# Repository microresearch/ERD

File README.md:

# ERD

ERD/ERD and ERD/SIR eurorack modules design and code files...

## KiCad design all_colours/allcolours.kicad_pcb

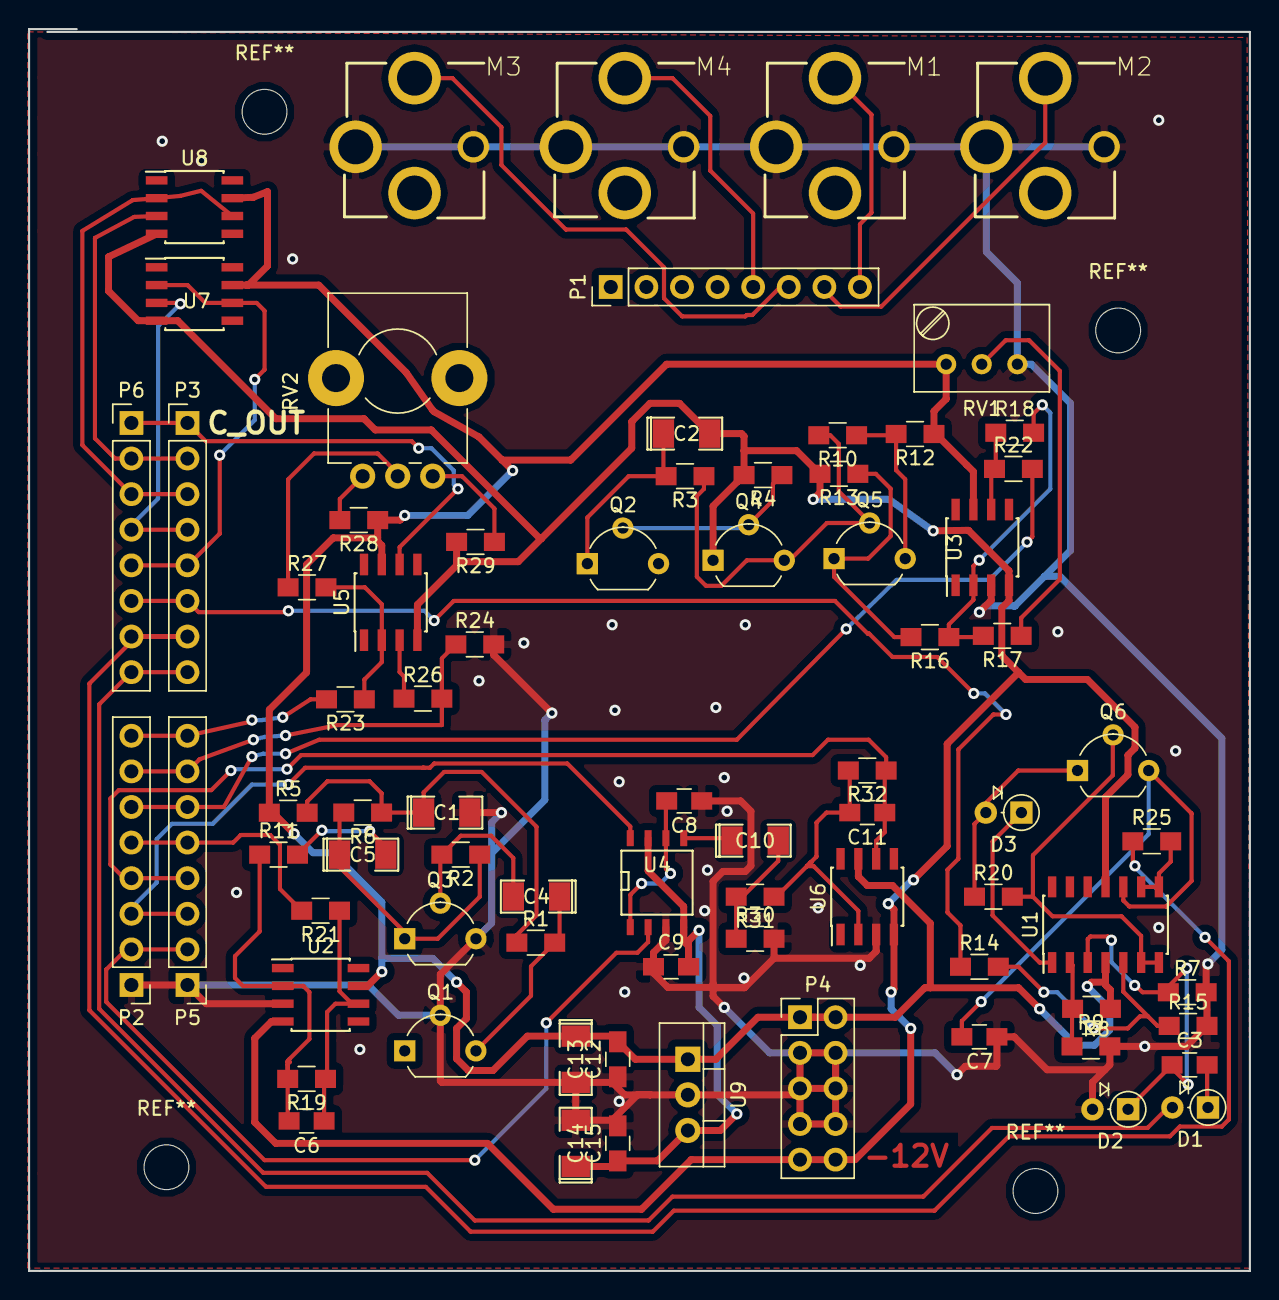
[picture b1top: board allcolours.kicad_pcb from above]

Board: 2 copper layers, 87.1 x 88.6 mm, 77 parts (0 on the bottom side), 56 nets.

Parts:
C1, C4: 47u; SMD-1206_Pol
C2, C5, C10, C13, C14: 10u; SMD-1206_Pol
C3: 1n; C_0805_HandSoldering
C6: 10p; C_0805_HandSoldering
C7, C8, C9, C12, C15: 100N; C_0805_HandSoldering
C11: 18p; C_0805_HandSoldering
D1, D2, D3: 1n4148; D_DO-35_SOD27_P2.54mm_Vertical_AnodeUp
M1, M2, M3, M4: AUDIO-JACKERTHENVAR; ERTHENVAR-JACK
P1, P2, P3, P5, P6: CONN_01X08; Pin_Header_Straight_1x08_Pitch2.54mm
P4: CONN_02X05; Pin_Header_Straight_2x05_Pitch2.54mm
Q1, Q3: Q_NPN_CBE; TO-92_Molded_Wide
Q2, Q4, Q5: Q_NPN_EBC; TO-92_Molded_Wide
Q6: BF245C_GSD; TO-92_Molded_Wide
R1, R3: 47K; R_0805_HandSoldering
R2: 150K; R_0805_HandSoldering
R4: 180K; R_0805_HandSoldering
R5, R12: 22R; R_0805_HandSoldering
R6, R9, R10, R23, R26, R28, R29: 10K; R_0805_HandSoldering
R7, R8, R15, R16, R17, R18, R24, R27: 100K; R_0805_HandSoldering
R11: 33k; R_0805_HandSoldering
R13: 2.2K; R_0805_HandSoldering
R14: 100R; R_0805_HandSoldering
R19: 470k; R_0805_HandSoldering
R20: 2.2M; R_0805_HandSoldering
R21, R22, R25: 1K; R_0805_HandSoldering
R30, R32: 39K; R_0805_HandSoldering
R31: 5.6K; R_0805_HandSoldering
RV1: 100K; Potentiometer_Trimmer_Bourns_3299W
RV2: POT; Potentiometer_Alps_RK09K_Horizontal
U1: TL074; SOIC-14_3.9x8.7mm_Pitch1.27mm
U2, U3, U5, U6, U7, U8: TL071; SOIC-8_3.9x4.9mm_Pitch1.27mm
U4: maxim_7400; SOIC-8-N
U9: 7805; TO-220_Vertical

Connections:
+12V: C12.2, C13.1, P4.1, P4.2, R5.1, R8.1, R12.1, R28.1, RV1.1, U1.4, U2.7, U3.7, U5.7, U6.7, U7.7, U8.7, U9.1
-12VA: C2.2, P4.9, P4.10, Q4.1, R4.2, R13.2, R29.2, U1.11, U2.4, U3.4, U5.4, U6.4, U7.4, U8.4
/5V: C9.2, C14.1, C15.1, U4.4, U4.7, U9.3
/7400_CLK_IN: P2.3, P5.3, U4.8
/7400_IN: P2.2, P5.2, U4.2
/7400_OUT: C11.1, P2.4, P5.4, R32.1, U6.6
/COMP_CV0: P2.8, P5.8, R23.2
/COMP_IN0: P2.7, P5.7, R24.1, R26.2
/COMP_OUT0: P3.1, P6.1, U5.6
/H_NOISE_OUT: P2.6, P5.6, R22.2
/SH_CLOCK: D1.2, P3.8, P6.8
/SH_IN: P3.6, P6.6, R14.1
/SH_OUT: P3.7, P6.7, R25.1
/Y_NOISE_OUT: P2.5, P5.5, R21.2
/buffer_in: P3.2, P6.2, U8.3
/buffer_in1: P3.4, P6.4, U7.3
/buffer_out: P3.3, P6.3, U8.2, U8.6
/buffer_out1: P3.5, P6.5, U7.2, U7.6
GND: C1.2, C7.1, C8.1, C9.1, C12.1, C13.2, C14.2, C15.2, D2.2, M1.1@1, M1.1@2, M2.1@1, M2.1@2, M3.1@1, M3.1@2, M4.1@1, M4.1@2, P2.1, P4.3, P4.4, P4.5, P4.6, P4.7, P4.8, P5.1, Q1.2, Q3.3, R7.2, R9.2, R15.2, R24.2, R30.2, RV1.3, U2.3, U3.3, U4.3, U6.3, U9.2
unnamed: C1.1, R1.1, R5.2, R6.1
unnamed: C2.1, Q2.1, R3.2
unnamed: C3.1, D2.1, R7.1, U1.3
unnamed: C3.2, D1.1
unnamed: C4.1, Q1.3, R1.2
unnamed: C4.2, Q3.2, R2.2
unnamed: C5.1, Q3.1, R2.1, R6.2
unnamed: C5.2, R11.2
unnamed: C6.1, R19.1, R21.1, U2.6
unnamed: C6.2, R11.1, R19.2, U2.2
unnamed: C7.2, Q6.3, U1.10
unnamed: C8.2, U4.1, U4.6
unnamed: C10.1, U4.5
unnamed: C10.2, R30.1, R31.2
unnamed: C11.2, R31.1, R32.2, U6.2
unnamed: D3.1, U1.1
unnamed: D3.2, Q6.1, R20.1
unnamed: M1.3, P1.8
unnamed: M2.3, P1.7
unnamed: M3.3, P1.6
unnamed: M4.3, P1.5
unnamed: Q2.2, Q4.2, R4.1
unnamed: Q4.3, Q5.2, R3.1, R10.2
unnamed: Q5.1, R13.1, R16.2
unnamed: Q5.3, R10.1, R12.2
unnamed: Q6.2, R20.2, U1.6, U1.7
unnamed: R8.2, R9.1, U1.2
unnamed: R14.2, R15.1, U1.5
unnamed: R16.1, R17.2, R18.2, U3.2
unnamed: R17.1, RV1.2
unnamed: R18.1, R22.1, U3.6
unnamed: R23.1, R27.2, U5.2
unnamed: R25.2, U1.8, U1.9
unnamed: R26.1, U5.3
unnamed: R27.1, RV2.2
unnamed: R28.2, RV2.3
unnamed: R29.1, RV2.1

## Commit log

2015-12-23 WRONG CODE before was uploaded....!
2016-01-18 first vampire
2016-02-05 vampire_board_001 now as swopped ext/.in etc
2016-02-09 vampire_brd_001 is base pcb, vampire_panel is top pcb/panel, vampire-brd_panel_stripped_forform.svg is perspex
2016-03-02 fixes
2016-10-29 adding new worm version/tm
2016-12-30 changed adc_init order
2017-02-15 latest!
2017-02-17 bug fixes and still stress testing/ T60
2017-02-20 T60 ?
2017-03-16 Latest ERD/SIR code for upload..
2017-03-16 The latest ERD/SIR to flash!
2017-03-20 latest
2017-07-19 added all colours
2018-06-25 added latest worm version of ERD/SIR hex
2018-06-25 added erd-sir panel
2018-06-25 added gerbers for erd/sir
2018-06-25 ERD/ERD original gerbers
2018-06-28 added parts
2018-06-28 hex for latest worm version
2018-06-28 layout and updated bom
2018-06-28 original ERD/ERD layout
2019-01-28 erd schematic pdf ++
2019-03-04 pulses
2019-08-15 layout with 1k options
